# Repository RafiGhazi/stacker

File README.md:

Inspired By Arcade Game called "Stacker" 

Using  a 32x8 LED matrix module that controlled by MAX7219 and push Button for interfacing with the user.

Schematics and PCB design are available, open the folder if you want to develop it to final design.

there's also wokw integrated visual studio code if you want to use a simulation but i wouldnt recommend to use it since idk why in wokwi it start LED matrix with the top row not the bottom.

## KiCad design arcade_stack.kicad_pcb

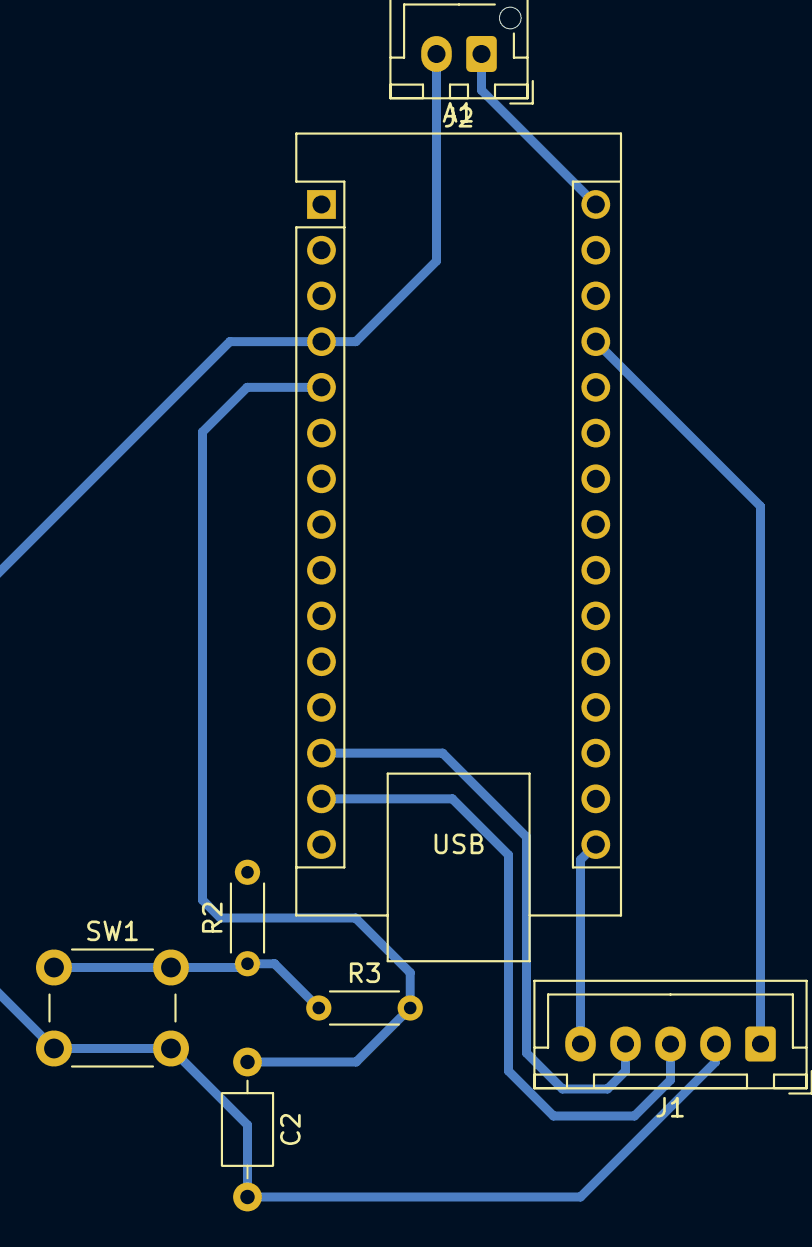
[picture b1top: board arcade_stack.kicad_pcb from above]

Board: 2 copper layers, 7 parts (0 on the bottom side), 8 nets.

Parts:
A1: Arduino_Nano_v3.x; Arduino_Nano
C2: C; C_Axial_L3.8mm_D2.6mm_P7.50mm_Horizontal
J1: Conn_01x05_Socket; JST_XH_B5B-XH-A_1x05_P2.50mm_Vertical
J2: Conn_01x02_Socket; JST_XH_B2B-XH-AM_1x02_P2.50mm_Vertical
R2, R3: R; R_Axial_DIN0204_L3.6mm_D1.6mm_P5.08mm_Horizontal
SW1: SW_Push; SW_PUSH_6mm

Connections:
+5V: A1.27 (+5V), J1.1, R2.2
Button: A1.5 (D2), C2.1, R3.2
CLK: A1.16 (D13), J1.5
CS: A1.13 (D10), J1.4
Din: A1.14 (D11), J1.3
GND: A1.4 (GND), C2.2, J1.2, J2.2, SW1.2
unnamed: R2.1, R3.1, SW1.1
VCC: A1.30 (VIN), J2.1

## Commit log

2026-02-03 Fix typo in README regarding Wokwi simulation
    Correct spelling of 'recommend' in the README.
